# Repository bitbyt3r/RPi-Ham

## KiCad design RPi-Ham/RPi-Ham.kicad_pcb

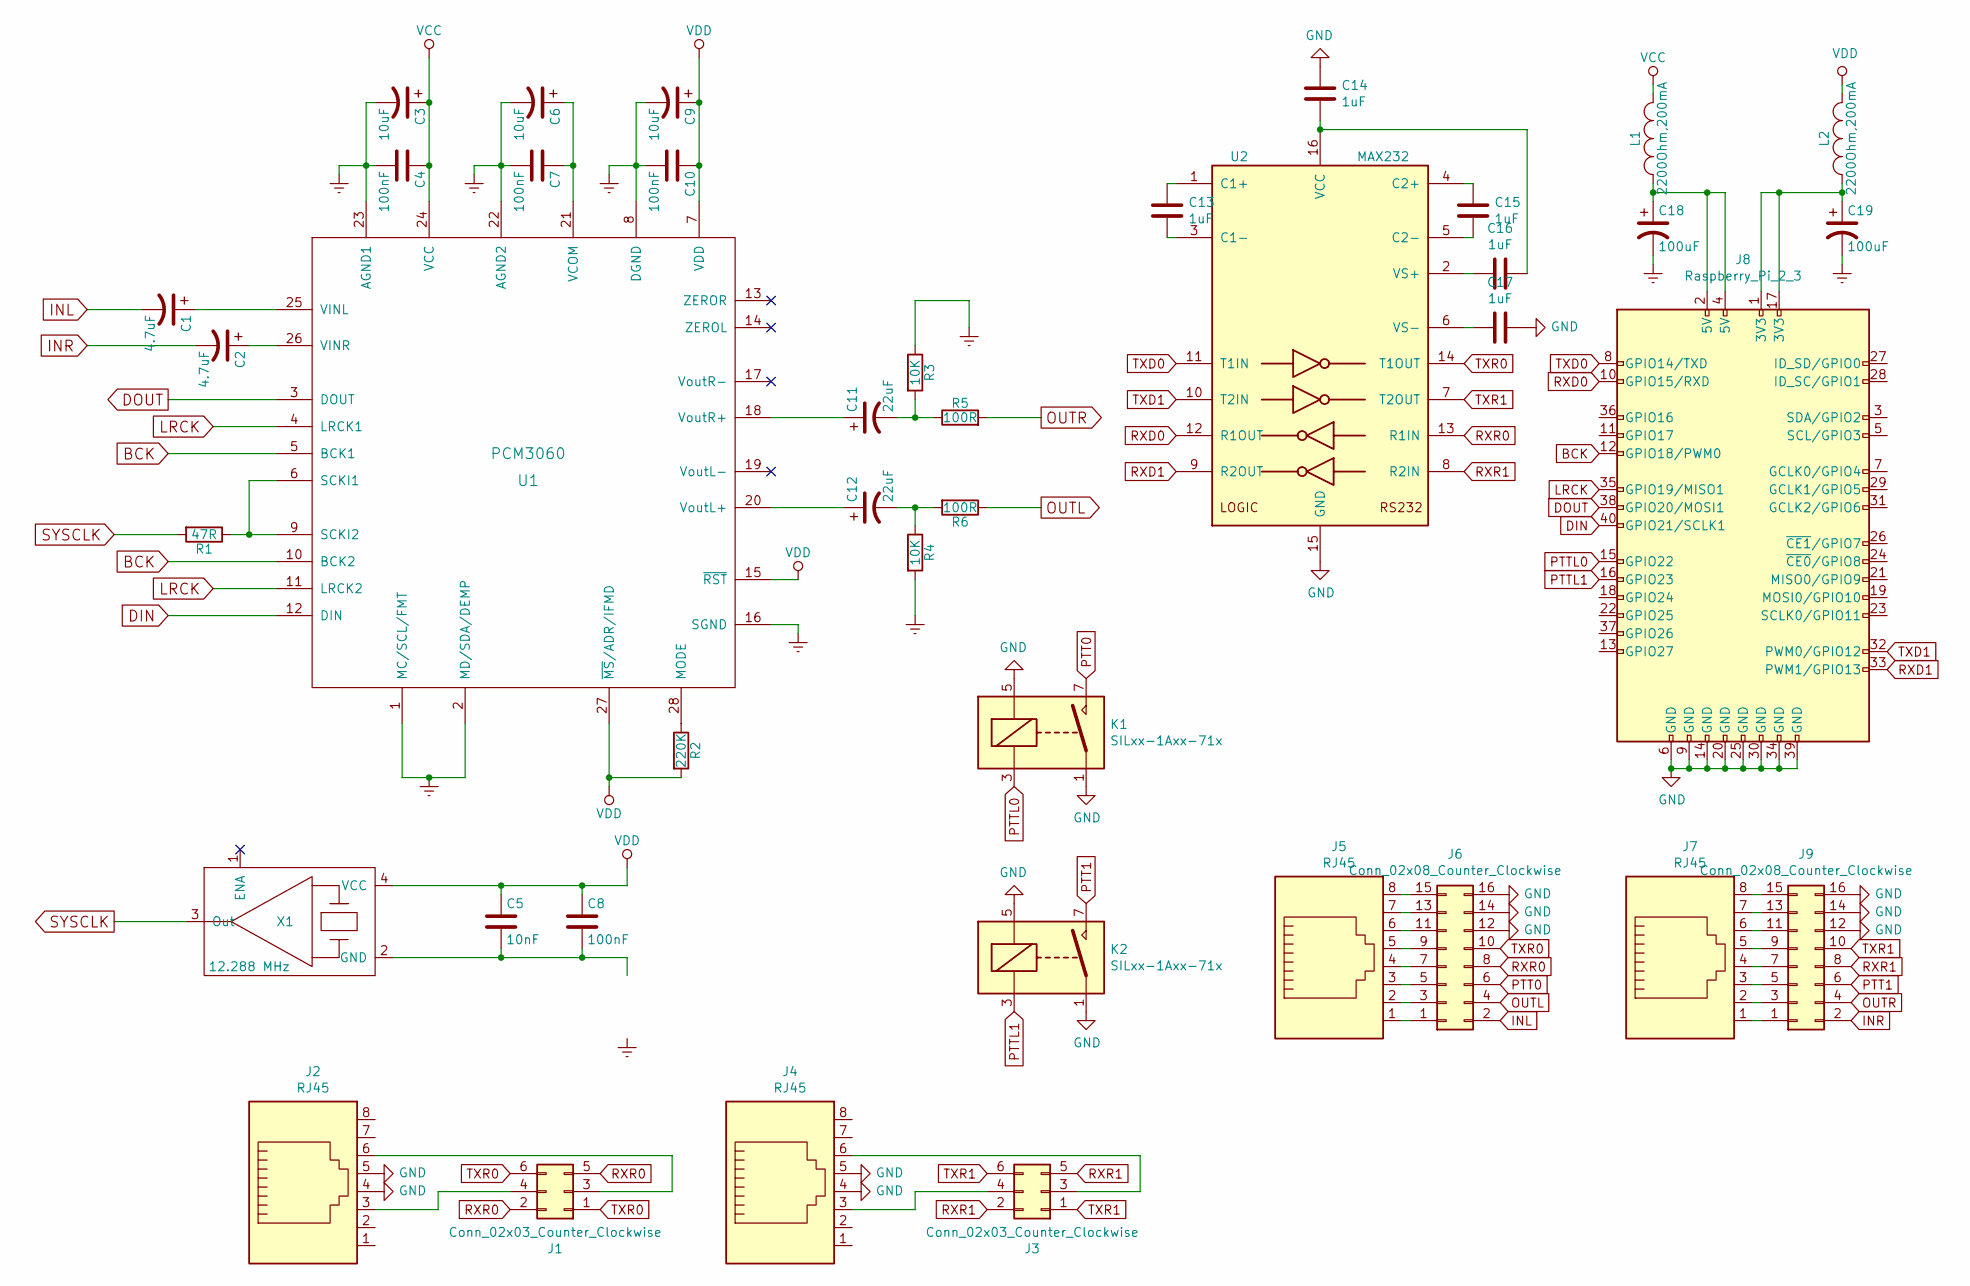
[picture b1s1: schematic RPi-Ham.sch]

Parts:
C1, C2: 4.7uF; C_0805_2012Metric_Pad1.15x1.40mm_HandSolder
C3, C6, C9: 10uF; C_0805_2012Metric_Pad1.15x1.40mm_HandSolder
C4, C7, C8, C10: 100nF; C_0805_2012Metric_Pad1.15x1.40mm_HandSolder
C5: 10nF; C_0805_2012Metric_Pad1.15x1.40mm_HandSolder
C11, C12: 22uF; C_0805_2012Metric_Pad1.15x1.40mm_HandSolder
C13, C14, C15, C16, C17: 1uF; C_0805_2012Metric_Pad1.15x1.40mm_HandSolder
C18, C19: 100uF; CP_Elec_6.3x5.4
J1, J3: Conn_02x03_Counter_Clockwise; PinHeader_2x03_P2.54mm_Vertical
J2, J4, J5, J7: RJ45; RJ45_Amphenol_54602-x08_Horizontal
J6, J9: Conn_02x08_Counter_Clockwise; PinSocket_2x08_P2.54mm_Vertical
J8: Raspberry_Pi_2_3; PinHeader_2x20_P2.54mm_Vertical
K1, K2: SILxx-1Axx-71x; Relay_SPST_StandexMeder_SIL_Form1A
L1, L2: 2200Ohm,200mA; R_0805_2012Metric_Pad1.15x1.40mm_HandSolder
R1: 47R; R_0805_2012Metric_Pad1.15x1.40mm_HandSolder
R2: 220K; R_0805_2012Metric_Pad1.15x1.40mm_HandSolder
R3, R4: 10K; R_0805_2012Metric_Pad1.15x1.40mm_HandSolder
R5, R6: 100R; R_0805_2012Metric_Pad1.15x1.40mm_HandSolder
U1: PCM3060; TSSOP-28_4.4x9.7mm_P0.65mm
U2: MAX232; SOIC-16_3.9x9.9mm_P1.27mm
X1: 12.288 MHz; Crystal_SMD_0603-4Pin_6.0x3.5mm_HandSoldering

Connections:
BCK: J8.12 (GPIO18/PWM0), U1.5 (BCK1), U1.10 (BCK2)
DIN: J8.40 (GPIO21/SCLK1), U1.12 (DIN)
DOUT: J8.38 (GPIO20/MOSI1), U1.3 (DOUT)
Earth: C3.2, C4.2, C6.2, C7.2, C9.2, C10.2, C18.2, C19.2, R3.1, R4.2, U1.1 (MC/SCL/FMT), U1.2 (MD/SDA/DEMP), U1.8 (DGND), U1.16 (SGND), U1.22 (AGND2), U1.23 (AGND1)
GND: C14.1, C17.1, J2.4, J2.5, J4.4, J4.5, J6.12, J6.14, J6.16, J8.6 (GND), J8.9 (GND), J8.14 (GND), J8.20 (GND), J8.25 (GND), J8.30 (GND), J8.34 (GND), J8.39 (GND), J9.12, J9.14, J9.16, K1.1, K1.5, K2.1, K2.5, U2.15 (GND)
INL: C1.2, J6.2
INR: C2.2, J9.2
LRCK: J8.35 (GPIO19/MISO1), U1.4 (LRCK1), U1.11 (LRCK2)
unnamed: C1.1, U1.25 (VINL)
unnamed: C2.1, U1.26 (VINR)
unnamed: C5.2, C8.2, X1.2 (GND)
unnamed: C6.1, C7.1, U1.21 (VCOM)
unnamed: C11.1, U1.18 (VoutR+)
unnamed: C11.2, R3.2, R5.1
unnamed: C12.1, U1.20 (VoutL+)
unnamed: C12.2, R4.1, R6.2
unnamed: C13.1, U2.1 (C1+)
unnamed: C13.2, U2.3 (C1-)
unnamed: C14.2, C16.1, U2.16 (VCC)
unnamed: C15.1, U2.4 (C2+)
unnamed: C15.2, U2.5 (C2-)
unnamed: C16.2, U2.2 (VS+)
unnamed: C17.2, U2.6 (VS-)
unnamed: C18.1, J8.2 (5V), J8.4 (5V), L1.1
unnamed: C19.1, J8.1 (3V3), J8.17 (3V3), L2.1
unnamed: J1.3, J2.6
unnamed: J1.4, J2.3
unnamed: J3.3, J4.6
unnamed: J3.4, J4.3
unnamed: J5.1, J6.1
unnamed: J5.2, J6.3
unnamed: J5.3, J6.5
unnamed: J5.4, J6.7
unnamed: J5.5, J6.9
unnamed: J5.6, J6.11
unnamed: J5.7, J6.13
unnamed: J5.8, J6.15
unnamed: J7.1, J9.1
unnamed: J7.2, J9.3
unnamed: J7.3, J9.5
unnamed: J7.4, J9.7
unnamed: J7.5, J9.9
unnamed: J7.6, J9.11
unnamed: J7.7, J9.13
unnamed: J7.8, J9.15
unnamed: R1.1, U1.6 (SCKI1), U1.9 (SCKI2)
unnamed: R2.1, U1.28 (MODE)
OUTL: J6.4, R6.1
OUTR: J9.4, R5.2
PTT0: J6.6, K1.7
PTT1: J9.6, K2.7
PTTL0: J8.15 (GPIO22), K1.3
PTTL1: J8.16 (GPIO23), K2.3
RXD0: J8.10 (GPIO15/RXD), U2.12 (R1OUT)
RXD1: J8.33 (PWM1/GPIO13), U2.9 (R2OUT)
RXR0: J1.2, J1.5, J6.8, U2.13 (R1IN)
RXR1: J3.2, J3.5, J9.8, U2.8 (R2IN)
SYSCLK: R1.2, X1.3 (Out)
TXD0: J8.8 (GPIO14/TXD), U2.11 (T1IN)
TXD1: J8.32 (PWM0/GPIO12), U2.10 (T2IN)
TXR0: J1.1, J1.6, J6.10, U2.14 (T1OUT)
TXR1: J3.1, J3.6, J9.10, U2.7 (T2OUT)
VCC: C3.1, C4.1, L1.2, U1.24 (VCC)
VDD: C5.1, C8.1, C9.1, C10.1, L2.2, R2.2, U1.7 (VDD), U1.15 (~RST), U1.27 (~MS~/ADR/IFMD), X1.4 (VCC)

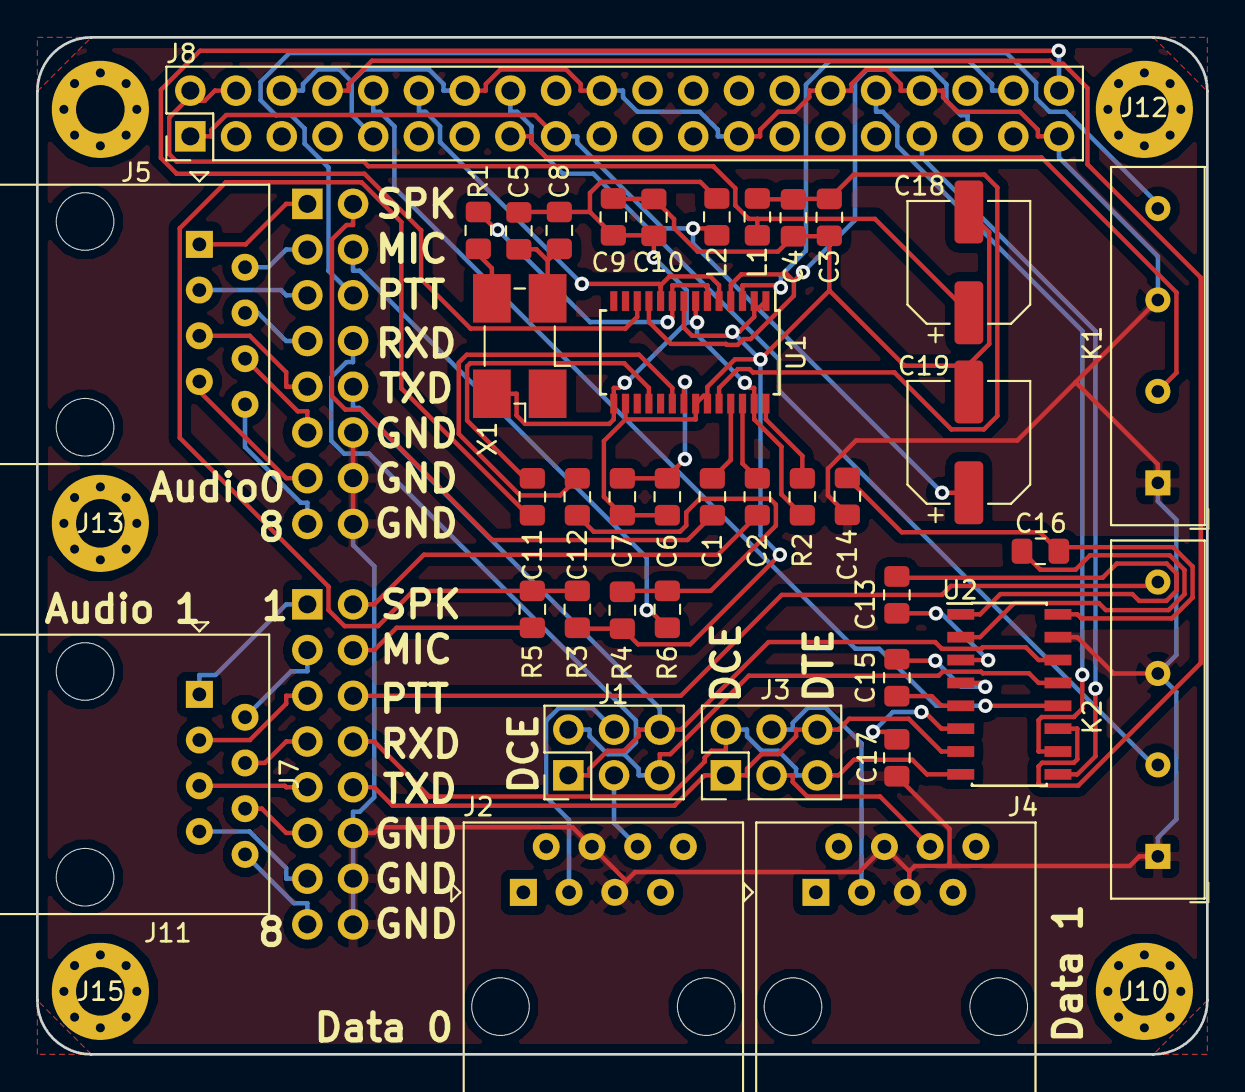
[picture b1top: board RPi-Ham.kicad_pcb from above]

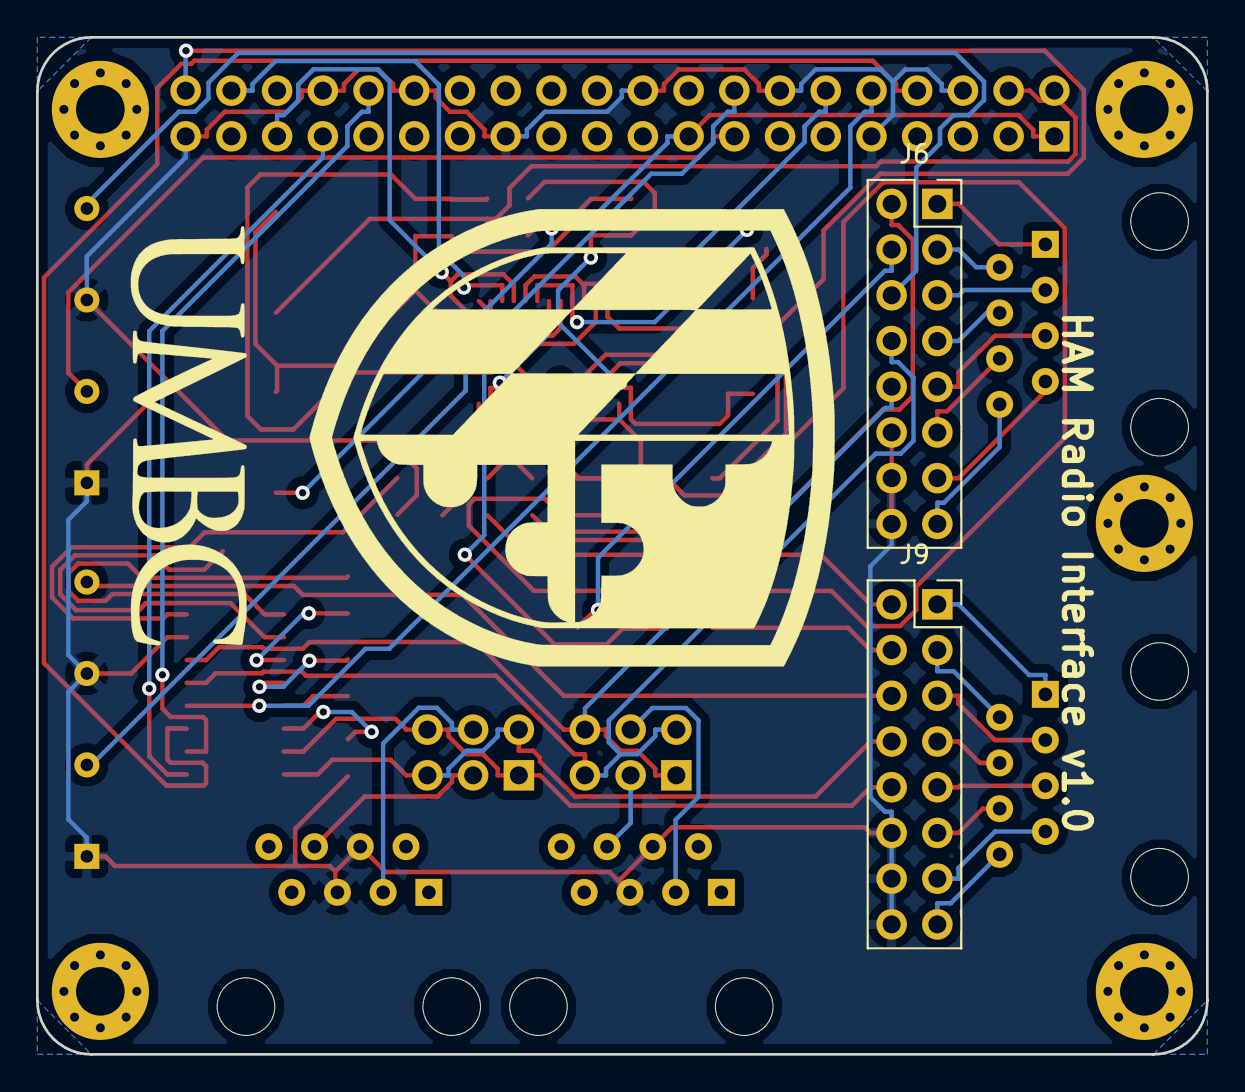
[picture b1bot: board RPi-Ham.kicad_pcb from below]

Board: 2 copper layers, 65.0 x 56.5 mm, 46 parts (2 on the bottom side), 64 nets.

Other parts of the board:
J10, J11, J12, J13, J15: MountingHole_2.7mm_M2.5_Pad_Via

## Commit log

2019-06-23 Added mount for pi zero
2019-06-23 Saved work
2019-06-23 Added PTT
